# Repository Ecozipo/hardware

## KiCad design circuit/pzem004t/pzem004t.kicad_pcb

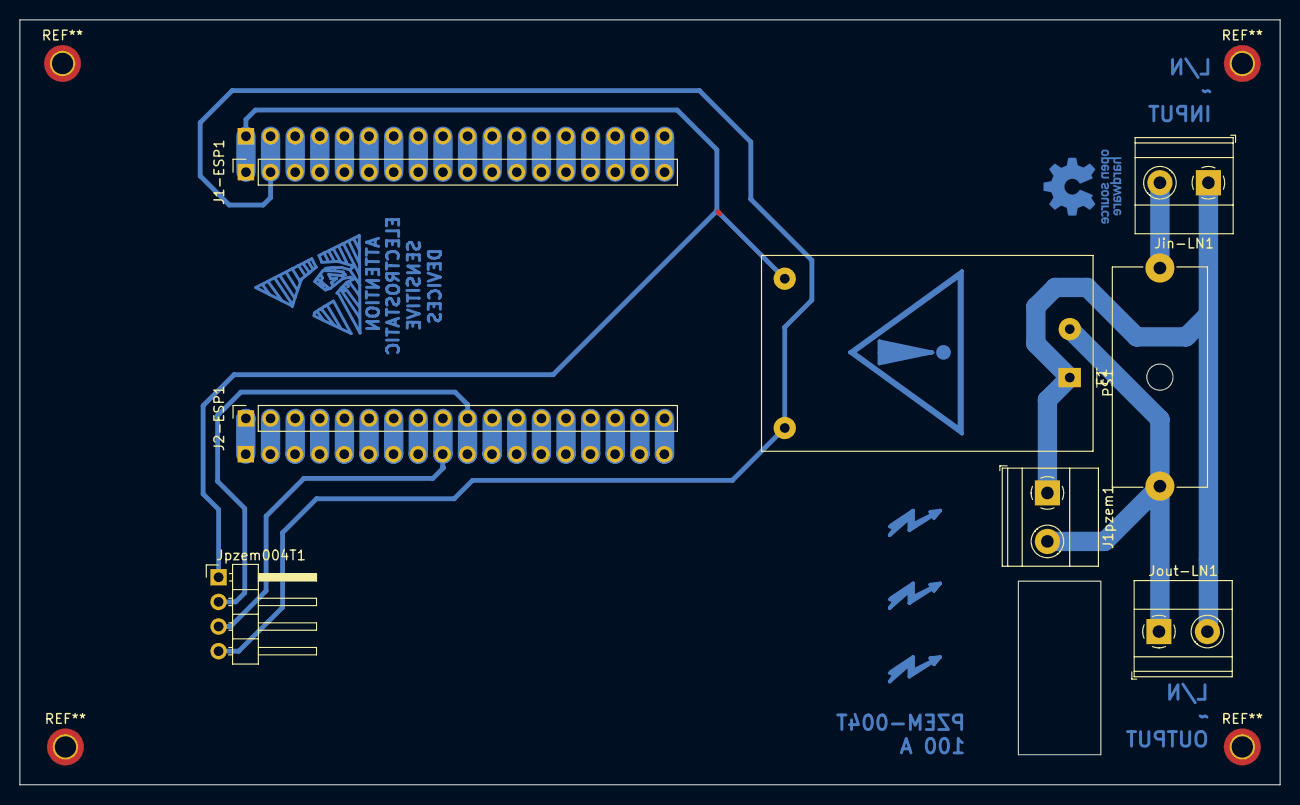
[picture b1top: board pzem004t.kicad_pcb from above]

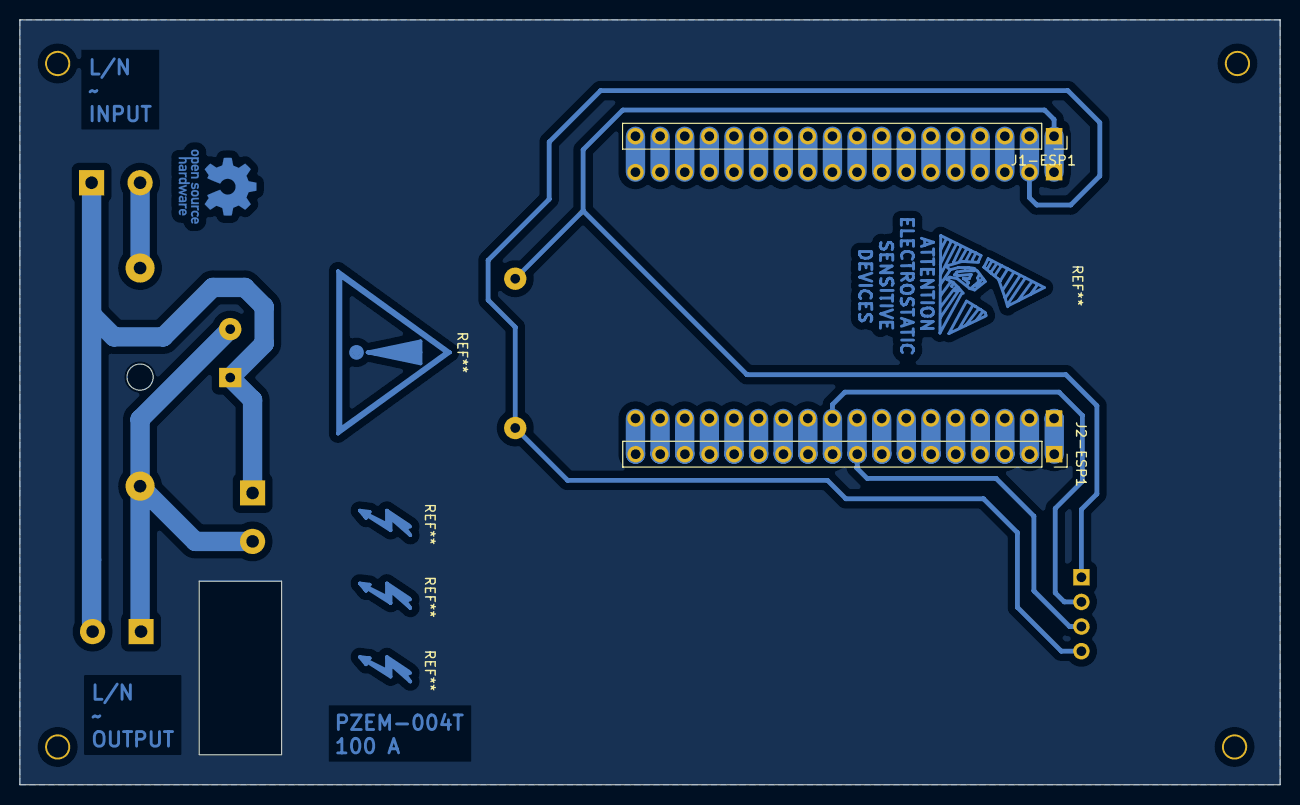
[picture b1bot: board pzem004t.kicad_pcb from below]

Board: 2 copper layers, 130.0 x 78.9 mm, 10 parts (2 on the bottom side), 39 nets.

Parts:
F1: Fuse; Fuseholder_Cylinder-5x20mm_Schurter_0031_8201_Horizontal_Op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
J1-ESP1, J1-ESP1#2, J2-ESP1, J2-ESP1#2: Conn_01x18_Socket; PinSocket_1x18_P2.54mm_Vertical
J1pzem1: Screw_Terminal_01x02; TerminalBlock_Phoenix_MKDS-1,5-2_1x02_P5.00mm_Horizontal
Jin-LN1: Screw_Terminal_01x02; TerminalBlock_Phoenix_MKDS-1,5-2_1x02_P5.00mm_Horizontal
Jout-LN1: Screw_Terminal_01x02; TerminalBlock_Phoenix_MKDS-1,5-2_1x02_P5.00mm_Horizontal
Jpzem004T1: Conn_01x04_Socket; PinHeader_1x04_P2.54mm_Horizontal
PS1: HLK-PM01; Converter_ACDC_HiLink_HLK-PMxx

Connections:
3.3Vesp: J2-ESP1.1, J2-ESP1#2.1
5V: J1-ESP1.1, J1-ESP1#2.1, Jpzem004T1.1, PS1.4 (+Vout)
CLKesp: J2-ESP1.2, J2-ESP1#2.2
CMDesp: J1-ESP1.3, J1-ESP1#2.3
D0esp: J2-ESP1.5, J2-ESP1#2.5
D2esp: J2-ESP1.7, J2-ESP1#2.7
D4esp: J2-ESP1.8, J2-ESP1#2.8
D5esp: J2-ESP1.11, J2-ESP1#2.11
D12esp: J1-ESP1.7, J1-ESP1#2.7
D13esp: J1-ESP1.6, J1-ESP1#2.6
D14esp: J1-ESP1.8, J1-ESP1#2.8
D15esp: J2-ESP1.6, J2-ESP1#2.6
D18esp: J2-ESP1.12, J2-ESP1#2.12
D19esp: J2-ESP1.13, J2-ESP1#2.13
D21esp: J2-ESP1.14, J2-ESP1#2.14
D22esp: J2-ESP1.17, J2-ESP1#2.17
D23esp: J2-ESP1.18, J2-ESP1#2.18
D25esp: J1-ESP1.11, J1-ESP1#2.11
D26esp: J1-ESP1.10, J1-ESP1#2.10
D27esp: J1-ESP1.9, J1-ESP1#2.9
D32esp: J1-ESP1.13, J1-ESP1#2.13
D33esp: J1-ESP1.12, J1-ESP1#2.12
D34esp: J1-ESP1.15, J1-ESP1#2.15
D35esp: J1-ESP1.14, J1-ESP1#2.14
ENesp: J1-ESP1.18, J1-ESP1#2.18
GNDesp: J1-ESP1.2, J1-ESP1#2.2, Jpzem004T1.4, PS1.3 (-Vout)
unnamed: J1pzem1.1, Jin-LN1.1, Jout-LN1.2, PS1.1 (AC/L)
unnamed: F1.1, J1pzem1.2, Jout-LN1.1, PS1.2 (AC/N)
unnamed: F1.2, Jin-LN1.2
RX0esp: J2-ESP1.15, J2-ESP1#2.15
RX2esp: J2-ESP1.9, J2-ESP1#2.9, Jpzem004T1.3
SD0esp: J2-ESP1.3, J2-ESP1#2.3
SD1esp: J2-ESP1.4, J2-ESP1#2.4
SD2esp: J1-ESP1.5, J1-ESP1#2.5
SD3esp: J1-ESP1.4, J1-ESP1#2.4
TX0esp: J2-ESP1.16, J2-ESP1#2.16
TX2esp: J2-ESP1.10, J2-ESP1#2.10, Jpzem004T1.2
VNesp: J1-ESP1.16, J1-ESP1#2.16
VPesp: J1-ESP1.17, J1-ESP1#2.17

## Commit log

2024-07-24 initial commit for hardware
2024-07-24 create components list and report
2024-07-24 add first item to componnent list
2024-07-24 add code to esp32 to connect to AWS IoT Core
2024-07-24 create template for report
2024-07-27 create secrets for aws iot configuration
2024-07-27 add lib and credentials to esp32
2024-08-02 Pio project update
2024-08-02 create pio code to connect to AWS
2024-08-08 new version of the project
2024-08-08 add test.h in include for pzem004t
2024-08-09 Ajout du code pour le PMZE
2024-08-09 Ajouter un Id unique pour chaque paquet envoyee a AWS_IOT_CORE
2024-08-09 Creer un nouveau PCB pour le compteur principale base sur le nouveau materiel PZME04T
2024-09-05 Migrate to aws iot core OSC2024_Spare
2024-09-11 handle switch and relay
2024-09-11 switch management
2024-09-16 Handle relay and switch
2024-09-16 Handle relay and switch updated
2024-10-09 MDP WIFI
2024-10-23 Moduleu Rano pour Spare
